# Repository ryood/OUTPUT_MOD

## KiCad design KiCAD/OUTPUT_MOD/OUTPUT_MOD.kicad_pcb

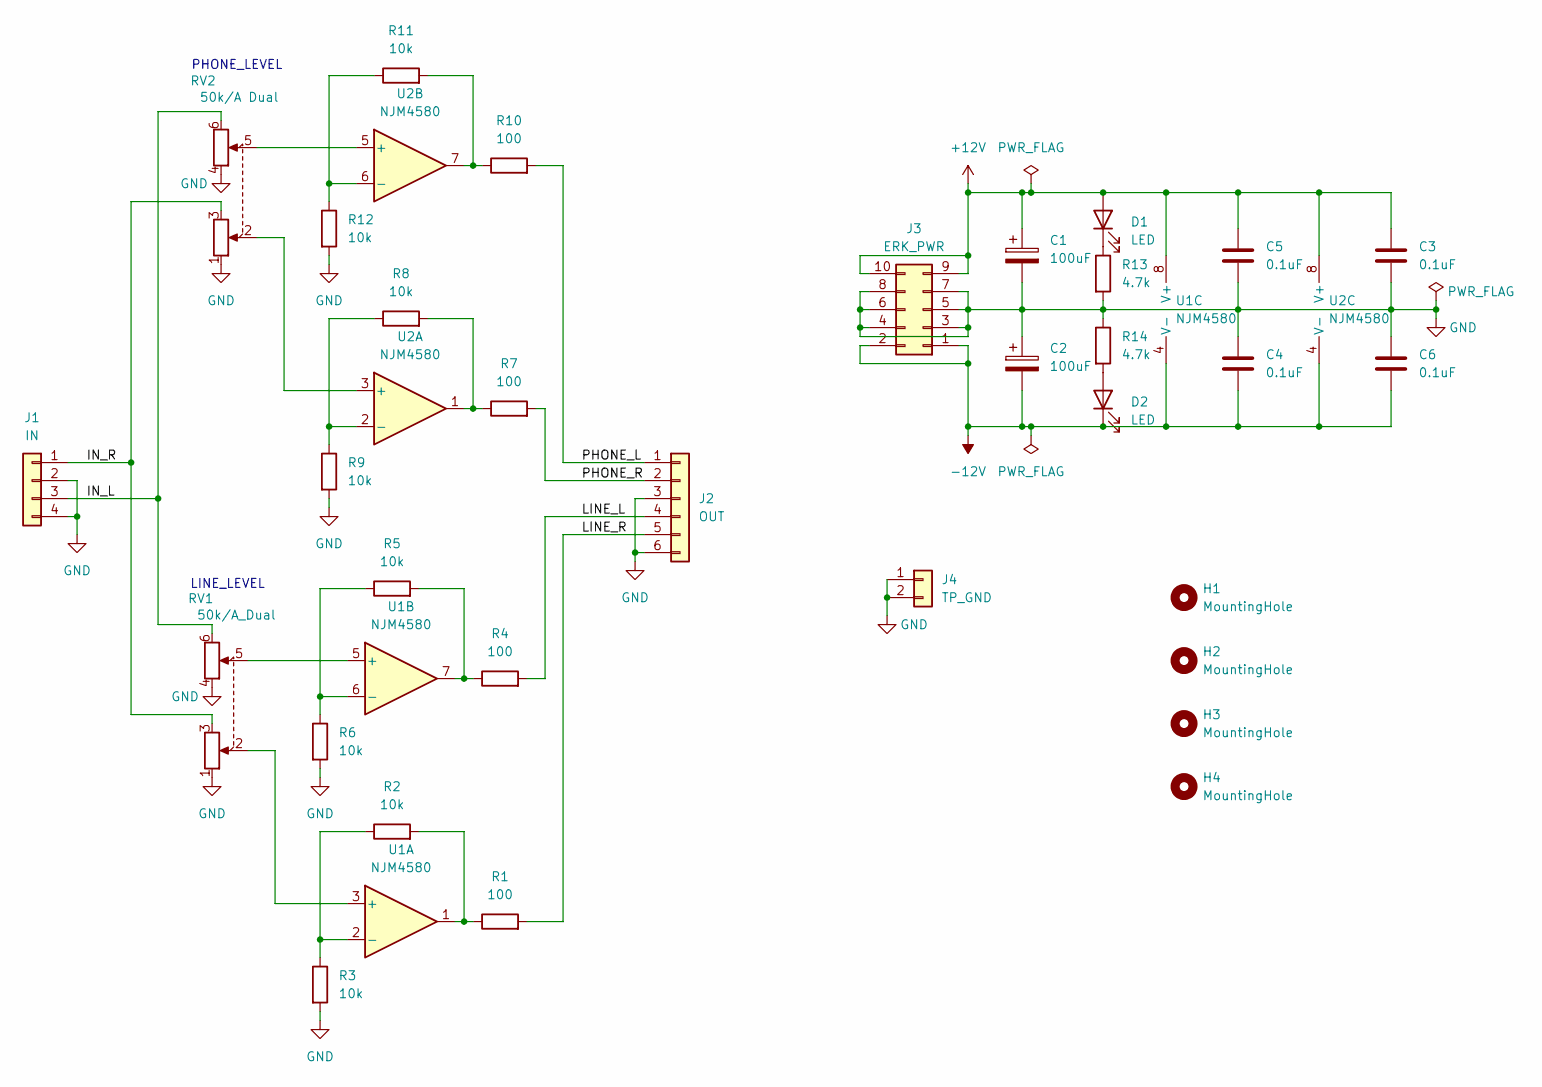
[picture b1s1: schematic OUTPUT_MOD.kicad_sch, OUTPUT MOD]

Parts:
C1, C2: 100uF; CP_Radial_D6.3mm_P2.50mm
C3, C4, C5, C6: 0.1uF; C_Disc_D3.0mm_W1.6mm_P2.50mm
D1, D2: LED; LED_D3.0mm
H1, H2, H3, H4: MountingHole; MountingHole_3.2mm_M3
J1: IN; JST_XH_B4B-XH-A_1x04_P2.50mm_Vertical
J2: OUT; JST_XH_B6B-XH-A_1x06_P2.50mm_Vertical
J3: ERK_PWR; IDC-Header_2x05_P2.54mm_Vertical
J4: TP_GND; PinHeader_1x02_P2.54mm_Vertical
R1, R4, R7, R10: 100; R_Axial_DIN0207_L6.3mm_D2.5mm_P10.16mm_Horizontal
R2, R3, R5, R6, R8, R9, R11, R12: 10k; R_Axial_DIN0207_L6.3mm_D2.5mm_P10.16mm_Horizontal
R13, R14: 4.7k; R_Axial_DIN0207_L6.3mm_D2.5mm_P10.16mm_Horizontal
RV1: 50k/A_Dual; Potentiometer_Alps_RK097_Dual_Horizontal
RV2: 50k/A Dual; Potentiometer_Alps_RK097_Dual_Horizontal
U1, U2: NJM4580; DIP-8_W7.62mm_Socket

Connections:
+12V: C1.1, C3.1, C5.1, D1.2 (A), J3.9, J3.10, U1.8 (V+), U2.8 (V+)
-12V: C2.2, C4.2, C6.2, D2.1 (K), J3.1, J3.2, U1.4 (V-), U2.4 (V-)
/IN_L: J1.3, RV1.6, RV2.6
/IN_R: J1.1, RV1.3, RV2.3
/LINE_L: J2.4, R4.2
/LINE_R: J2.5, R1.2
/PHONE_L: J2.1, R10.2
/PHONE_R: J2.2, R7.2
GND: C1.2, C2.1, C3.2, C4.1, C5.2, C6.1, J1.2, J1.4, J2.3, J2.6, J3.3, J3.4, J3.5, J3.6, J3.7, J3.8, J4.1, J4.2, R3.2, R6.2, R9.2, R12.2, R13.2, R14.1, RV1.1, RV1.4, RV2.1, RV2.4
unnamed: D1.1 (K), R13.1
unnamed: D2.2 (A), R14.2
unnamed: R1.1, R2.2, U1.1
unnamed: R2.1, R3.1, U1.2 (-)
unnamed: R4.1, R5.2, U1.7
unnamed: R5.1, R6.1, U1.6 (-)
unnamed: R7.1, R8.2, U2.1
unnamed: R8.1, R9.1, U2.2 (-)
unnamed: R10.1, R11.2, U2.7
unnamed: R11.1, R12.1, U2.6 (-)
unnamed: RV1.2, U1.3 (+)
unnamed: RV1.5, U1.5 (+)
unnamed: RV2.2, U2.3 (+)
unnamed: RV2.5, U2.5 (+)

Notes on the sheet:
PHONE_LEVEL
LINE_LEVEL

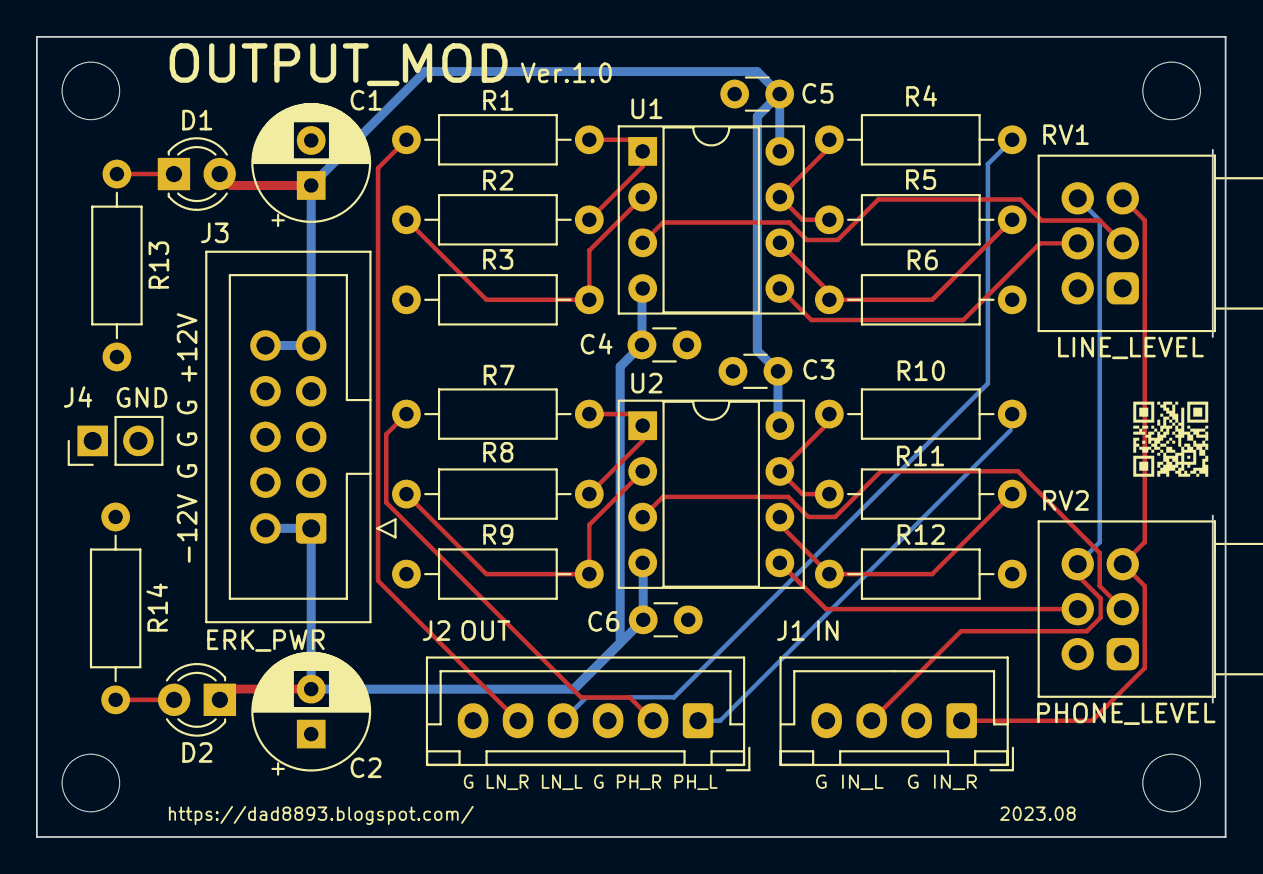
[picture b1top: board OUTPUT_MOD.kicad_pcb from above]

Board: 2 copper layers, 66.0 x 44.5 mm, 34 parts (0 on the bottom side), 23 nets.
